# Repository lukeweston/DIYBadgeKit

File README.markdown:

DIY educational LED badge soldering kit for Makerfaire Adelaide.

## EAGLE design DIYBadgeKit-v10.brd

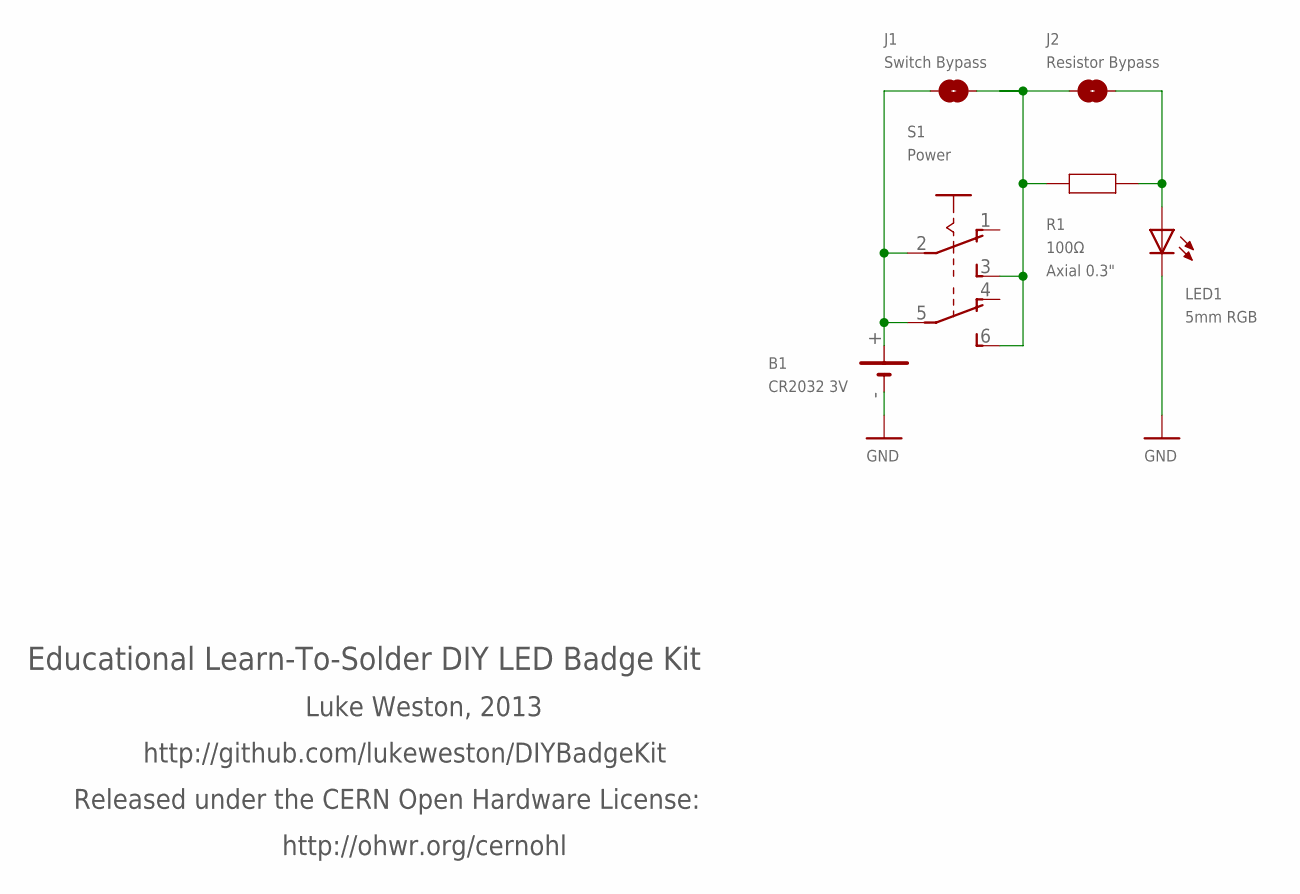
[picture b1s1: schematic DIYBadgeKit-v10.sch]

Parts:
B1: CR2032 3V; B2430UNI
J1: Switch Bypass; SJ
J2: Resistor Bypass; SJ
LED1: 5mm RGB; LED5MM
R1: 100Ω; AXIAL-0.3
S1: Power; A68-A31

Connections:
GND: B1.-, B1.-@1 (-), LED1.K (C)
J2: J2.2, LED1.A, R1.P$2 (2)
unnamed: J1.2, J2.1, R1.P$1 (1), S1.3 (S), S1.6 (S)
unnamed: B1.+, B1.+@1 (+), B1.+@2 (+), B1.+@3 (+), B1.+@4 (+), J1.1, S1.2, S1.5

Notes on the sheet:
Educational Learn-To-Solder DIY LED Badge Kit
Luke Weston, 2013
http://github.com/lukeweston/DIYBadgeKit
Released under the CERN Open Hardware License:
http://ohwr.org/cernohl

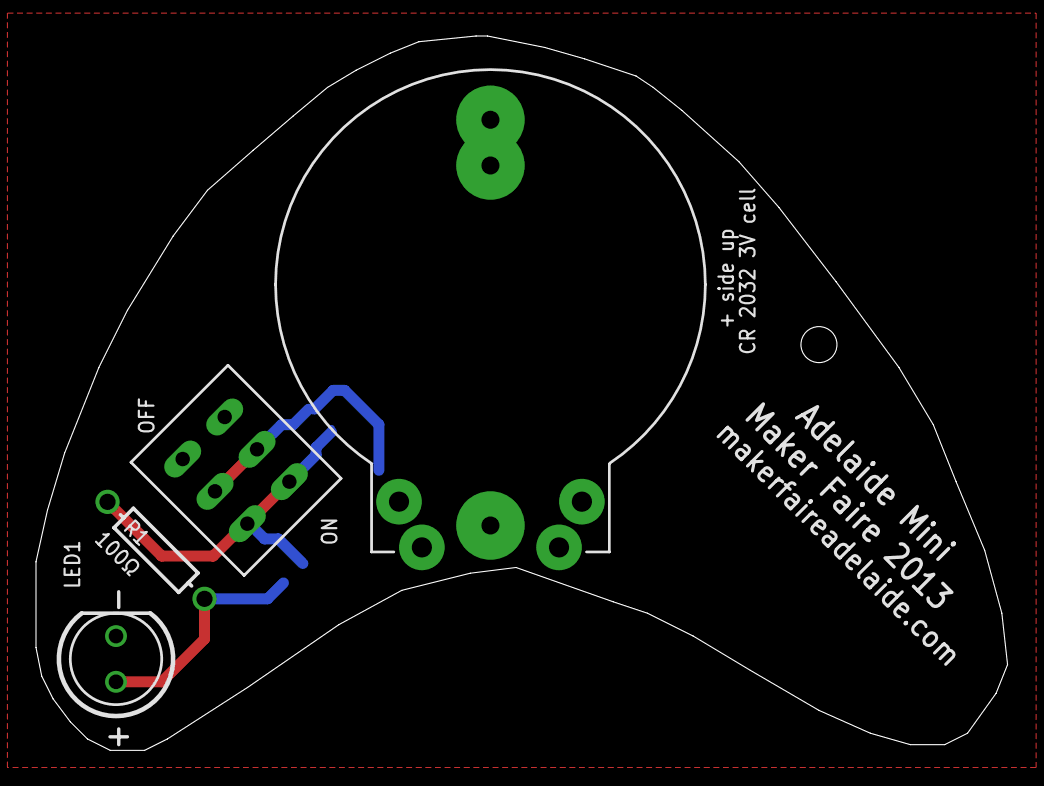
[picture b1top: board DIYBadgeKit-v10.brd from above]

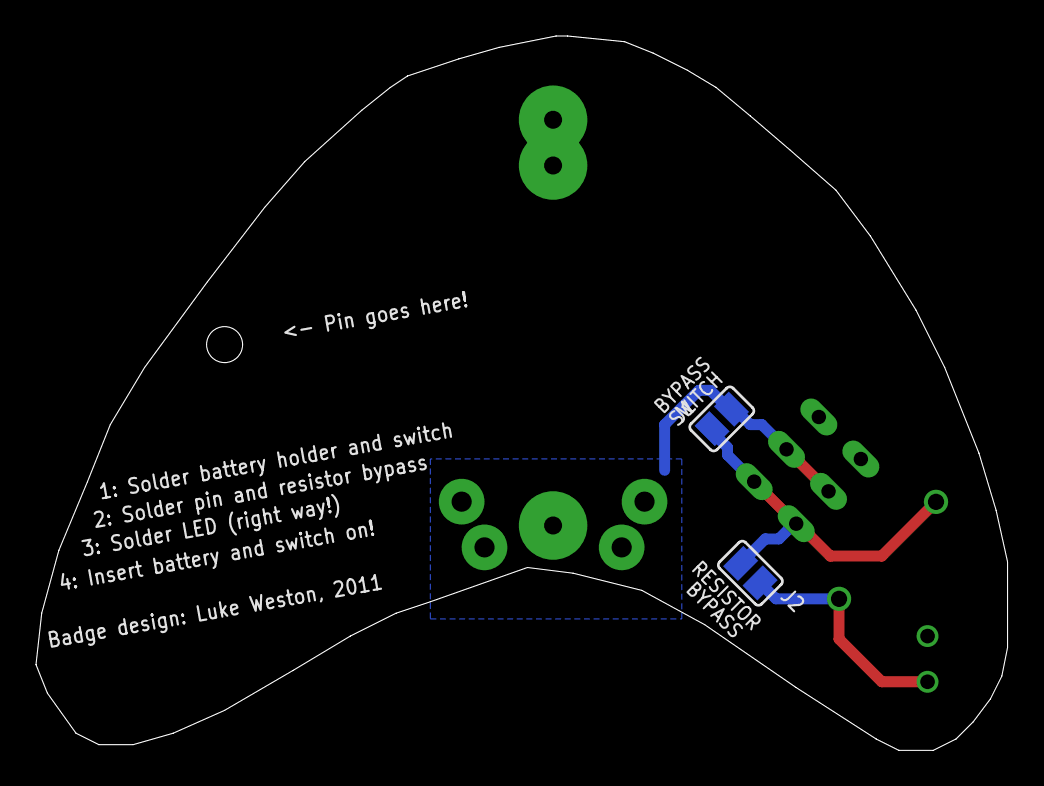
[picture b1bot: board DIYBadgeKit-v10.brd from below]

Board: 2 copper layers, 54.0 x 39.7 mm, 6 parts (2 on the bottom side), 4 nets.

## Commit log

2013-02-22 fixed readme image filename
